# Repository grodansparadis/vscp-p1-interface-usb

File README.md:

# vscp-p1-interface-usb
P1 HAN port interface &lt;-> USB

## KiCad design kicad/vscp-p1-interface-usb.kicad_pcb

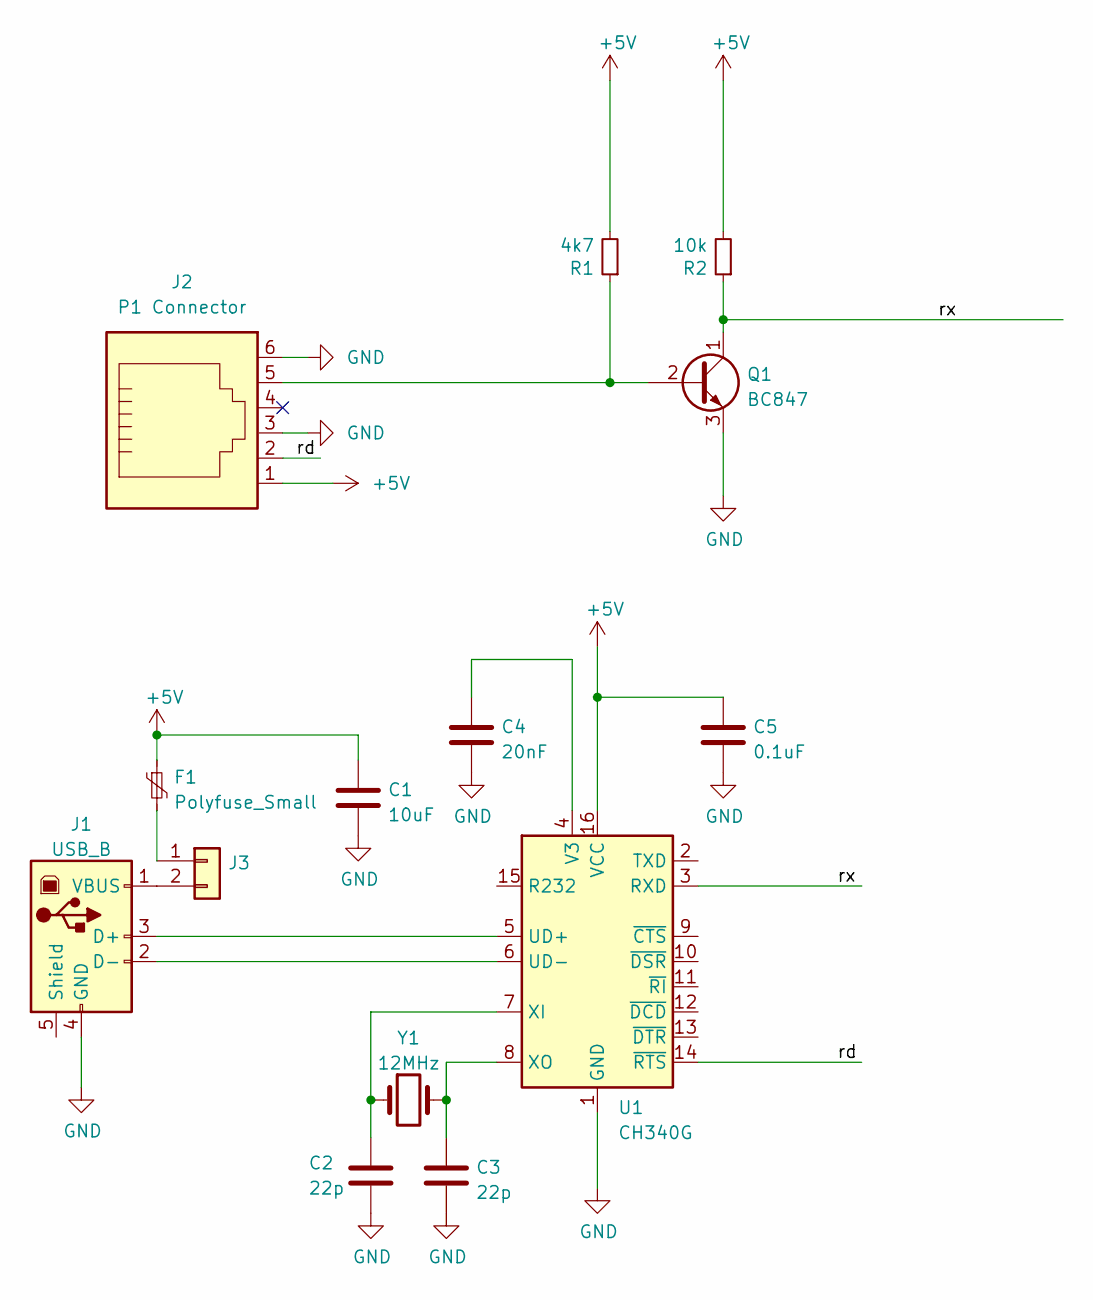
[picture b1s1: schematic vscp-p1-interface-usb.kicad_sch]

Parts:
C1: 10uF; C_0805_2012Metric_Pad1.18x1.45mm_HandSolder
C2, C3: 22p; C_0805_2012Metric_Pad1.18x1.45mm_HandSolder
C4: 20nF; C_0805_2012Metric_Pad1.18x1.45mm_HandSolder
C5: 0.1uF; C_0805_2012Metric_Pad1.18x1.45mm_HandSolder
F1: Polyfuse_Small; Fuse_0805_2012Metric_Pad1.15x1.40mm_HandSolder
J1: USB_B; USB_B_Amphenol_MUSB-D511_Vertical_Rugged
J2: P1 Connector; RJ12_Amphenol_54601
J3: Conn_01x02; PinHeader_1x02_P2.54mm_Vertical
Q1: BC847; TSOT-23_HandSoldering
R1: 4k7; R_0805_2012Metric_Pad1.20x1.40mm_HandSolder
R2: 10k; R_0805_2012Metric_Pad1.20x1.40mm_HandSolder
U1: CH340G; SOIC-16_3.9x9.9mm_P1.27mm
Y1: 12MHz; Crystal_SMD_HC49-SD_HandSoldering

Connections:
+5V: C1.1, C5.1, F1.1, J2.1, R1.2, R2.2, U1.16 (VCC)
/rd: J2.2, U1.14 (~RTS)
/rx: Q1.1 (C), R2.1, U1.3 (RXD)
GND: C1.2, C2.2, C3.2, C4.2, C5.2, J1.4 (GND), J2.3, J2.6, Q1.3 (E), U1.1 (GND)
unnamed: C2.1, U1.7 (XI), Y1.1
unnamed: C3.1, U1.8 (XO), Y1.2
unnamed: C4.1, U1.4 (V3)
unnamed: F1.2, J3.1
unnamed: J1.1 (VBUS), J3.2
unnamed: J1.2 (D-), U1.6 (UD-)
unnamed: J1.3 (D+), U1.5 (UD+)
unnamed: J2.5, Q1.2 (B), R1.1

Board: 2 copper layers, 14 parts (0 on the bottom side), 12 nets, no tracks yet.

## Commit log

2022-09-07 Rename project
2022-09-07 Initial checkin
2022-09-07 Added component docs
